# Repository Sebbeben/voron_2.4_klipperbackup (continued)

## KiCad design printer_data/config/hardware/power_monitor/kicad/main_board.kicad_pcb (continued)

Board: 2 copper layers, 160 parts (38 on the bottom side), 79 nets, no tracks yet.

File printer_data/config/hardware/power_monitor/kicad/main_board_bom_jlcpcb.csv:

Comment,Designator,Footprint,LCSC Part #,MPN,Qty
24V IN,J1,"TerminalBlock_Phoenix_MKDS-1,5-2-5.08_1x02_P5.08mm_Horizontal",C8465,Kangnex WJ500V-5.08-2P,1
SMBJ24A,D1,D_SMB,C224017,Littelfuse SMBJ24A,1
10u 50V,"C14,C15",C_1210_3225Metric,C138687,Samsung CL32B106KBJNNNE,2
5V IN,J2,"TerminalBlock_Phoenix_MKDS-1,5-2-5.08_1x02_P5.08mm_Horizontal",C8465,Kangnex WJ500V-5.08-2P,1
SMBJ6.0A,D2,D_SMB,C113976,MDD SMBJ6.0A,1
10u,C16,C_1206_3216Metric,C14860,Samsung CL31B106KAHNNNE,1
100n 50V,"C1,C2,C3,C4,C5,C6,C7,C8,C9",C_0603_1608Metric,C346191,Samsung CL10B104KB8NFNC,9
1,"R1,R2,R3,R4,R5,R6,R7,R8,R9,R10,R11,R12,R13,R14,R15,R16,R17,R18",R_0603_1608Metric,C22936,UNI-ROYAL 0603WAF100KT5E,18
10m,"RS1,RS8",R_2512_6332Metric,C375688,YAGEO PA2512FKE7W0R01E,2
5m,RS2,R_2512_6332Metric,C5375417,Milliohm HoYLR2512-2W-5mR-1%,1
20m,"RS3,RS6,RS7,RS9",R_2512_6332Metric,C7420049,FOJAN FRM252WFR020TN,4
INA3221AIRGVR,"U1,U2,U3",Texas_RGV0016A_VQFN-16-1EP_4x4mm_P0.65mm_EP2.1x2.1mm,C181255,TI INA3221AIRGVR,3
100n,"C10,C11,C12,C31,C41,C43",C_0603_1608Metric,C346191,Samsung CL10B104KB8NFNC,6
50m,"RS4,RS5",R_2512_6332Metric,C7420008,FOJAN FRM252WFR050TN,2
CLIP F1 10A,"F1A,F1B",Fuseclip_Blade_Mini_Keystone_3557,C2680614,Keystone 3557,2
SPIDER 24V,J3,"TerminalBlock_Phoenix_MKDS-1,5-2-5.08_1x02_P5.08mm_Horizontal",C8465,Kangnex WJ500V-5.08-2P,1
10k,"R19,R20,R60,R61,R62,R64,R87,RL1,RL2,RL3,RL4,RL5,RL6",R_0603_1608Metric,C25804,UNI-ROYAL 0603WAF1002T5E,13
red,"LEDF1,LEDF2,LEDF3,LEDF4,LEDF5,LEDF6,LEDF7",LED_0603_1608Metric,C2286,KENTO KT-0603R,7
CLIP F2 5A,"F2A,F2B",Fuseclip_Blade_Mini_Keystone_3557,C2680614,Keystone 3557,2
SB2040 24V,J4,"TerminalBlock_Phoenix_MKDS-1,5-2-5.08_1x02_P5.08mm_Horizontal",C8465,Kangnex WJ500V-5.08-2P,1
CLIP F3 3A,"F3A,F3B",Fuseclip_Blade_Mini_Keystone_3557,C2680614,Keystone 3557,2
CHAMBER FANS 24V,J5,"TerminalBlock_Phoenix_MKDS-1,5-2-5.08_1x02_P5.08mm_Horizontal",C8465,Kangnex WJ500V-5.08-2P,1
CLIP F4 3A,"F4A,F4B",Fuseclip_Blade_Mini_Keystone_3557,C2680614,Keystone 3557,2
NEVERMORE 24V,J6,"TerminalBlock_Phoenix_MKDS-1,5-2-5.08_1x02_P5.08mm_Horizontal",C8465,Kangnex WJ500V-5.08-2P,1
CLIP F5 3A,"F5A,F5B",Fuseclip_Blade_Mini_Keystone_3557,C2680614,Keystone 3557,2
LIGHTS 24V,J7,"TerminalBlock_Phoenix_MKDS-1,5-2-5.08_1x02_P5.08mm_Horizontal",C8465,Kangnex WJ500V-5.08-2P,1
CLIP F6 3A,"F6A,F6B",Fuseclip_Blade_Mini_Keystone_3557,C2680614,Keystone 3557,2
SPARE 24V,J8,"TerminalBlock_Phoenix_MKDS-1,5-2-5.08_1x02_P5.08mm_Horizontal",C8465,Kangnex WJ500V-5.08-2P,1
CLIP F7 5A,"F7A,F7B",Fuseclip_Blade_Mini_Keystone_3557,C2680614,Keystone 3557,2
PI 5V,J9,"TerminalBlock_Phoenix_MKDS-1,5-2-5.08_1x02_P5.08mm_Horizontal",C8465,Kangnex WJ500V-5.08-2P,1
1k,"R65,RL7",R_0603_1608Metric,C21190,UNI-ROYAL 0603WAF1001T5E,2
AP2112K-3.3,U12,SOT-23-5,C51118,Diodes AP2112K-3.3TRG1,1
1u,"C17,C42",C_0603_1608Metric,C15849,Samsung CL10A105KB8NNNC,2
10u,"C13,C30",C_0805_2012Metric,C15850,Samsung CL21A106KAYNNNE,2
600R@100MHz,FB1,L_0603_1608Metric,C85833,Murata BLM18KG601SN1D,1
4u7,C40,C_0805_2012Metric,C1779,Samsung CL21A475KAQNNNE,1
STM32G071KBT6,U10,LQFP-32_7x7mm_P0.8mm,C529348,ST STM32G071KBT6,1
RESET,SW1,SW_Push_1P1T_XKB_TS-1187A,C318884,XKB TS-1187A-B-A-B,1
green,"LED10,LED11",LED_0603_1608Metric,C12624,KENTO KT-0603G,2
RJ45 from CT board,J20,RJ45_Kinghelm_KH-RJ45-58_Shielded_Horizontal,C2683360,kinghelm KH-RJ45-58-8P8C,1
10k 0.1%,"R70,R71,R73",R_0603_1608Metric,C95204,YAGEO RT0603BRD0710KL,3
AC 9V IN,J21,BarrelJack_Horizontal,C2961147,CUI PJ-002AH,1
120k,R72,R_0603_1608Metric,C25808,UNI-ROYAL 0603WAF1203T5E,1
100k,"R79,R80,R81,R82,R84,R86",R_0603_1608Metric,C25803,UNI-ROYAL 0603WAF1003T5E,6
2k2,"R74,R75,R76,R77,R78",R_0603_1608Metric,C4190,UNI-ROYAL 0603WAF2201T5E,5
10n C0G,"C35,C36,C37,C38,C39",C_0603_1608Metric,C76599,TDK C1608C0G1H103JT000N,5
BAV99,"D10,D11,D12,D13,D14",SOT-23,C2500,"Nexperia BAV99,215",5
TO PI,J10,JST_XH_B6B-XH-A_1x06_P2.50mm_Vertical,C144397,JST B6B-XH-A(LF)(SN),1
TO SPIDER INPUT,J11,JST_XH_B2B-XH-A_1x02_P2.50mm_Vertical,C158012,JST B2B-XH-A(LF)(SN),1
1A,F8,Fuse_1206_3216Metric,C151135,Littelfuse 0466001.NRHF,1
SS14,D15,D_SMA,C2480,MDD SS14,1
HEATER RELAY COIL,J12,"TerminalBlock_Phoenix_MKDS-1,5-2-5.08_1x02_P5.08mm_Horizontal",C8465,Kangnex WJ500V-5.08-2P,1
AO3400A,"Q1,Q2",SOT-23,C20917,AOS AO3400A,2
100,"R83,R85",R_0603_1608Metric,C22775,UNI-ROYAL 0603WAF1000T5E,2

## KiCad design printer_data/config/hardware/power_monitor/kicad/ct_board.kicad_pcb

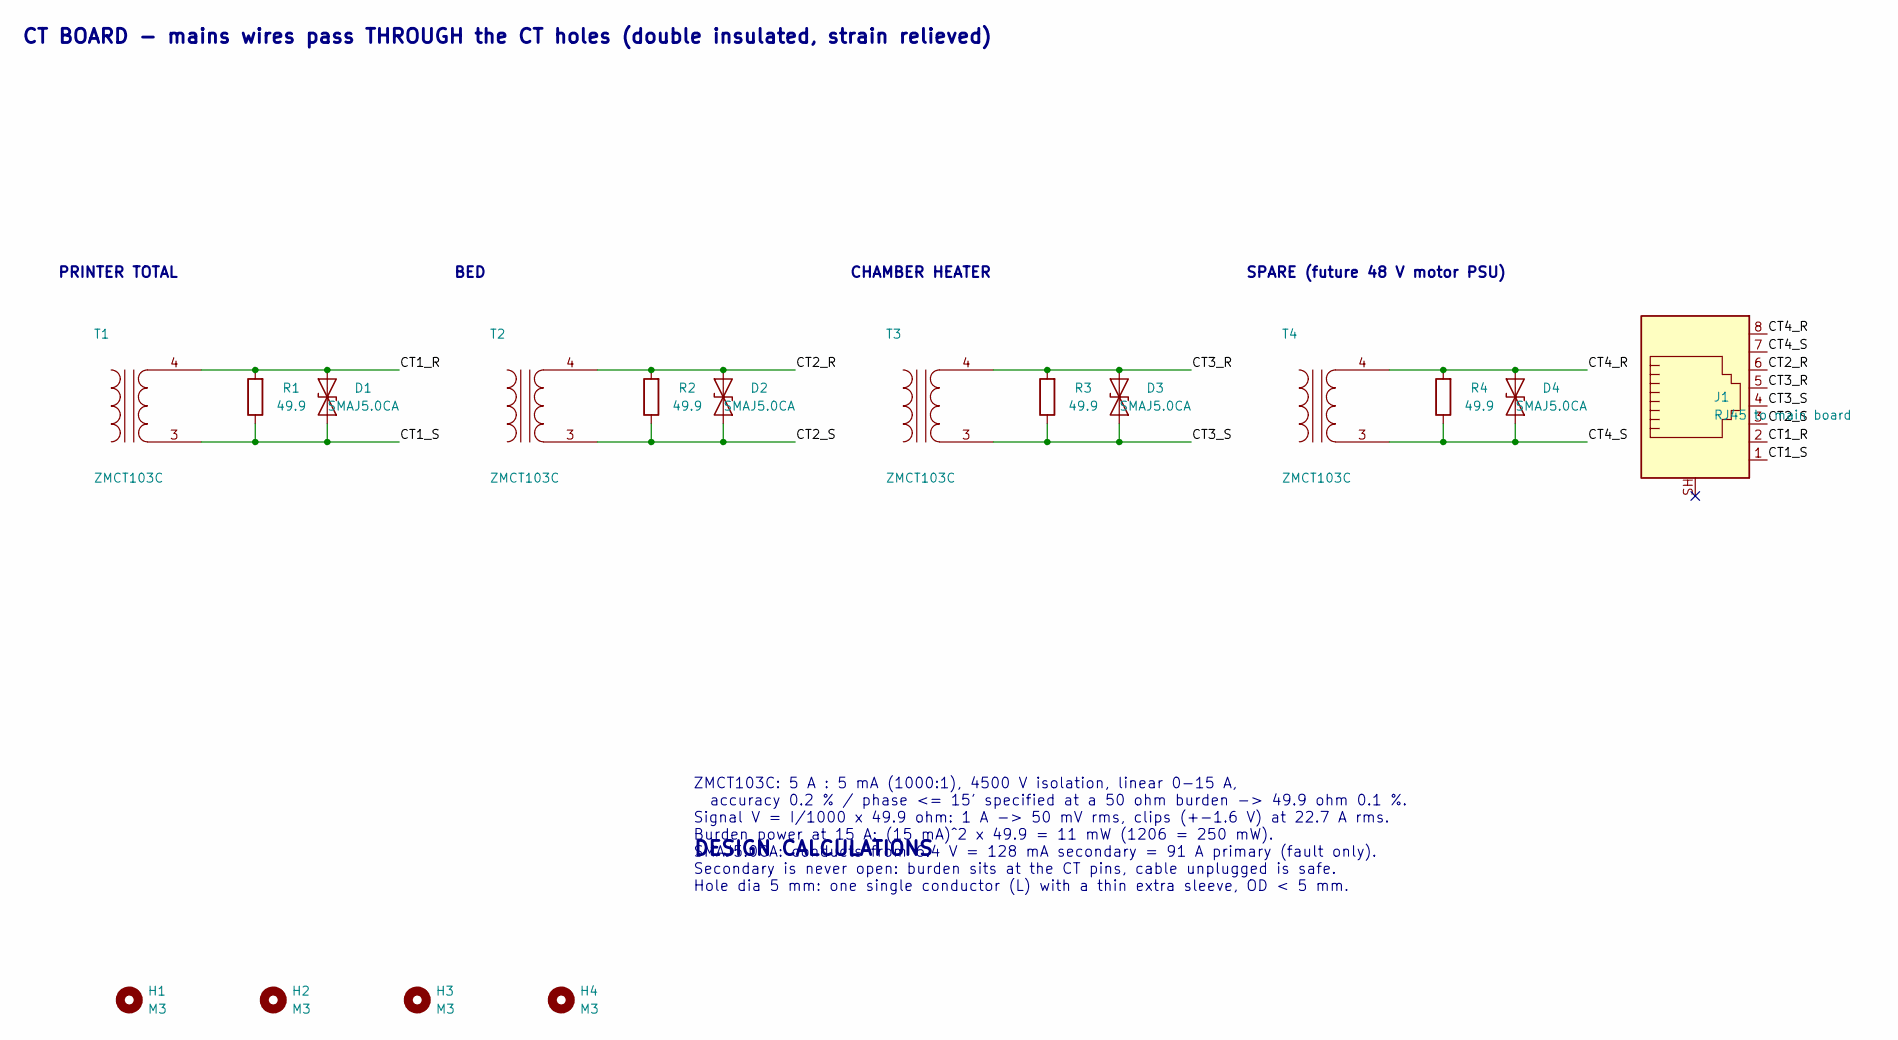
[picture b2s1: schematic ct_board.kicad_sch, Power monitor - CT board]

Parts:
D1, D2, D3, D4: SMAJ5.0CA; D_SMA; MPN LGE SMAJ5.0CA; LCSC C320524
H1, H2, H3, H4: M3; MountingHole_3.2mm_M3
J1: RJ45 to main board; RJ45_Kinghelm_KH-RJ45-58_Shielded_Horizontal; MPN kinghelm KH-RJ45-58-8P8C; LCSC C2683360
R1, R2, R3, R4: 49.9; R_1206_3216Metric; MPN RESI PTFR1206B49R9P9; LCSC C479116
T1, T2, T3, T4: ZMCT103C; MPN ZHE MING LANG XI ZMCT103C; LCSC C94571

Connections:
CT1_R: D1.2 (A2), J1.2, R1.2, T1.4 (SB)
CT1_S: D1.1 (A1), J1.1, R1.1, T1.3 (SA)
CT2_R: D2.2 (A2), J1.6, R2.2, T2.4 (SB)
CT2_S: D2.1 (A1), J1.3, R2.1, T2.3 (SA)
CT3_R: D3.2 (A2), J1.5, R3.2, T3.4 (SB)
CT3_S: D3.1 (A1), J1.4, R3.1, T3.3 (SA)
CT4_R: D4.2 (A2), J1.8, R4.2, T4.4 (SB)
CT4_S: D4.1 (A1), J1.7, R4.1, T4.3 (SA)

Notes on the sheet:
CT BOARD - mains wires pass THROUGH the CT holes (double insulated, strain relieved)
PRINTER TOTAL
BED
CHAMBER HEATER
SPARE (future 48 V motor PSU)
DESIGN CALCULATIONS
ZMCT103C: 5 A : 5 mA (1000:1), 4500 V isolation, linear 0-15 A, accuracy 0.2 % / phase <= 15' specified at a 50 ohm burden -> 49.9 ohm 0.1 %. Signal V = I/1000 x 49.9 ohm: 1 A -> 50 mV rms, clips (+-1.6 V) at 22.7 A rms. Burden power at 15 A: (15 mA)^2 x 49.9 = 11 mW (1206 = 250 mW). SMAJ5.0CA: con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

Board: 2 copper layers, 17 parts (0 on the bottom side), 8 nets, no tracks yet.

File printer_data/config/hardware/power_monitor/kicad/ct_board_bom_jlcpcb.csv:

Comment,Designator,Footprint,LCSC Part #,MPN,Qty
ZMCT103C,"T1,T2,T3,T4",ZMCT103C,C94571,ZHE MING LANG XI ZMCT103C,4
49.9,"R1,R2,R3,R4",R_1206_3216Metric,C479116,RESI PTFR1206B49R9P9,4
SMAJ5.0CA,"D1,D2,D3,D4",D_SMA,C320524,LGE SMAJ5.0CA,4
RJ45 to main board,J1,RJ45_Kinghelm_KH-RJ45-58_Shielded_Horizontal,C2683360,kinghelm KH-RJ45-58-8P8C,1

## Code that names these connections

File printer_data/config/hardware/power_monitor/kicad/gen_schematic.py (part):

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
# STM32G071KxT (GP version, no N suffix) differs from the KxTxN (PD version) that KiCad has a
# symbol for: DS12232 Rev 3 figure 7. Only the in-stock KBT6 (C529348) is a GP part.
GP_PIN_NAMES = {"17": "PB2", "26": "PA15", "27": "PB3", "28": "PB4", "29": "PB5"}

def stm32_gp_symbol():
    b = kilib.flat_symbol("MCU_ST_STM32G0", "STM32G071KBTxN")
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    out.append(b[pos:])
    b = "".join(out)
    b = re.sub(r'\(property "Value" "[^"]*"', '(property "Value" "STM32G071KBTx"', b, 1)
    b = re.sub(r'\(property "Description" "[^"]*"', '(property "Description" "STM32G071KBT6 LQFP-32 GP version (DS12232 fig. 7): pin 17 PB2, 26-29 PA15/PB3/PB4/PB5"', b, 1)
    return b

def ct_symbol():
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    mcu_nets = {
        "4": W, "5": W, "6": W,
        "7": "ADC_V", "8": "ADC_CT1", "15": "ADC_CT2", "16": "ADC_CT3", "14": "ADC_CT4",
        "11": "PA4_NSS", "10": "PA3_RX2", "21": "PA10_RX1", "32": "HEATER_EN_MCU",
        "30": "SCL", "31": "SDA", "18": "CRITICAL", "17": "LED_STAT",
        "24": "SWDIO", "25": "SWCLK",
    }
    e = s.part("PowerMonitor:STM32G071KBTx", "U10", "STM32G071KBT6", mx, my, mcu_nets,
               "Package_QFP:LQFP-32_7x7mm_P0.8mm", "C529348", "ST STM32G071KBT6",
               note="PA0=V, PA1/PB0/PB1/PA7=CT1-4 (all FT_a; PA5 is TT_a, no positive injection), PB6/PB7=I2C1 (= ROM bootloader I2C1, addr 0x51), PB8=heater relay enable",
               fields=((5.08, -33.02, "left"), (5.08, -30.48, "left")))
    vdd, vss, nrst = e["4"], e["5"], e["6"]
    s.w(vdd, (vdd[0], vdd[1] - 2.54))
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                fields=((-2.54, -1.27, "right"), (-2.54, 1.27, "right")))
    gnd(s, *ec["2"])
    # bootloader pin pull-ups (G07x bootloader V11.3 issue) + NSS idle high
    # AN2606 Rev 62 table 91: bootloader USART RX = PA10 (USART1), PA3 (USART2), PC11 (USART3, not
    # bonded on LQFP-32); SPI1 NSS = PA4. Pull them high so the bootloader only reacts to I2C1.
    xp = mx + 55.88
    s.text("Bootloader pins idle high (AN2606 Rev 62 table 91)", xp - 5.08, my - 33.02, 1.27)
    for i, net in enumerate(["PA3_RX2", "PA10_RX1", "PA4_NSS"]):
        x = xp + i * 12.7
        ec = s.vput("Device:R", "R%d" % (60 + i), "10k", "1", x, my - 25.4, {"1": "+3V3_MCU", "2": W},
                    footprint=FP_R0603, lcsc="C25804", mpn="UNI-ROYAL 0603WAF1002T5E",
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           lcsc=LED_GREEN[0], mpn=LED_GREEN[1], note="Status LED (active high)")
    s.w((xp + 17.78, yl), (xp + 22.86, yl))
    s.lab("GND", xp + 22.86, yl, "R")
    # BOOT0 recovery: PA14 (SWCLK) -> 10k -> solder jumper -> 3V3
    yb = my + 15.24
    s.lab("SWCLK", xp - 5.08, yb, "L")
    s.w((xp - 5.08, yb), (xp, yb))
    s.hput("Device:R", "R64", "10k", "1", xp, yb, {"1": W, "2": W}, footprint=FP_R0603, lcsc="C25804",
           mpn="UNI-ROYAL 0603WAF1002T5E", note="BOOT0 recovery (needs nBOOT_SEL = 0): PA14 is BOOT0 on G0")
    s.w((xp + 7.62, yb), (xp + 10.16, yb))
    s.hput("Jumper:SolderJumper_2_Open", "JP1", "BOOT0", "1", xp + 10.16, yb, {"1": W, "2": W},
           footprint="Jumper:SolderJumper-2_P1.3mm_Open_RoundedPad1.0x1.5mm", in_bom=False,
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    s.part("Connector_Generic:Conn_01x06", "J10", "TO PI", bx + 25.4, by + 7.62,
           {"1": "GND", "2": "SDA", "3": "SCL", "4": "CRITICAL", "5": "WARNING", "6": "HEATER_EN_PI"},
           "Connector_JST:JST_XH_B6B-XH-A_1x06_P2.50mm_Vertical", "C144397", "JST B6B-XH-A(LF)(SN)",
           note="Pi: GND pin 9, SDA GPIO2 pin 3, SCL GPIO3 pin 5, alerts + HEATER_EN_PI to free GPIOs (>= GPIO9: pulled low at boot)",
           fields=((2.54, -2.54, "left"), (2.54, 12.7, "left")))
    s.part("Connector_Generic:Conn_01x02", "J11", "TO SPIDER INPUT", bx + 25.4, by + 33.02,
           {"1": "CRITICAL", "2": "GND"}, "Connector_JST:JST_XH_B2B-XH-A_1x02_P2.50mm_Vertical", "C158012",
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               fields=((0, -3.81, "center"), (0, 3.81, "center")))

    # ---- Block G: heater safety relay driver --------------------------------
    # Coil is energised only while BOTH the STM32 (PB8) and the Pi (J10 pin 6) drive their
    # enable high: two low-side MOSFETs in series. Reset / boot / crash / unplugged = coil off.
    # The relay/contactor itself (NO contacts, cuts only the heater supply) sits off-board.
    bx, by = 525.78, 320.04
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        gnd(s, *ep["2"])
        return q
    s.w((xc, yc), (xc, yc + 5.08)); s.j(xc, yc)
    q1 = fet("Q1", "Enable from STM32 PB8", yc + 5.08, "HEATER_EN_MCU", "R83", "R84")
    s.w(q1["2"], (xc, q1["2"][1] + 5.08))
    s.lab("RLY_MID", xc, q1["2"][1] + 2.54, "R")
    q2 = fet("Q2", "Enable from the Pi (J10 pin 6)", q1["2"][1] + 5.08, "HEATER_EN_PI", "R85", "R86")
    gnd(s, *q2["2"])

    # ---- Design calculations on the sheet (full version: ../design_calcs.py) ---
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        "  50 Hz (same on all channels -> cancels in V x I).",
        "  Fault (CT TVS 9.2 V around VBIAS): (1.65+9.2-3.3-0.8)",
        "  /2.2k = 3.1 mA into BAV99 (1k gave 6.75 mA). ADC pins",
        "  PA0/PA1/PA7/PB0/PB1 are FT_a: no positive injection,",
        "  -5 mA limit OK. PA5 (TT_a) not used.",
        "  100k CTx_S -> VBIAS: unplugged reads 0 A,",
        "  burden error 49.9/100k = 0.05 % (calibrated).",
        "",
        "I2C: 0x40/41/42 INA, 0x50 STM32 app, 0x51 ROM",
        "  bootloader (AN2606 Rev 62 tab 91: I2C1 PB6/PB7).",
        "  Bootloader USART RX PA10/PA3 + SPI1 NSS PA4 pulled",
        "  high; USART3 RX PC11 and SPI2 not on LQFP-32.",
        "  BOOT0 pin (JP1) is ignored until nBOOT_SEL = 0 is",
        "  written (factory 1, AN2606 pattern 11). Recovery",
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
